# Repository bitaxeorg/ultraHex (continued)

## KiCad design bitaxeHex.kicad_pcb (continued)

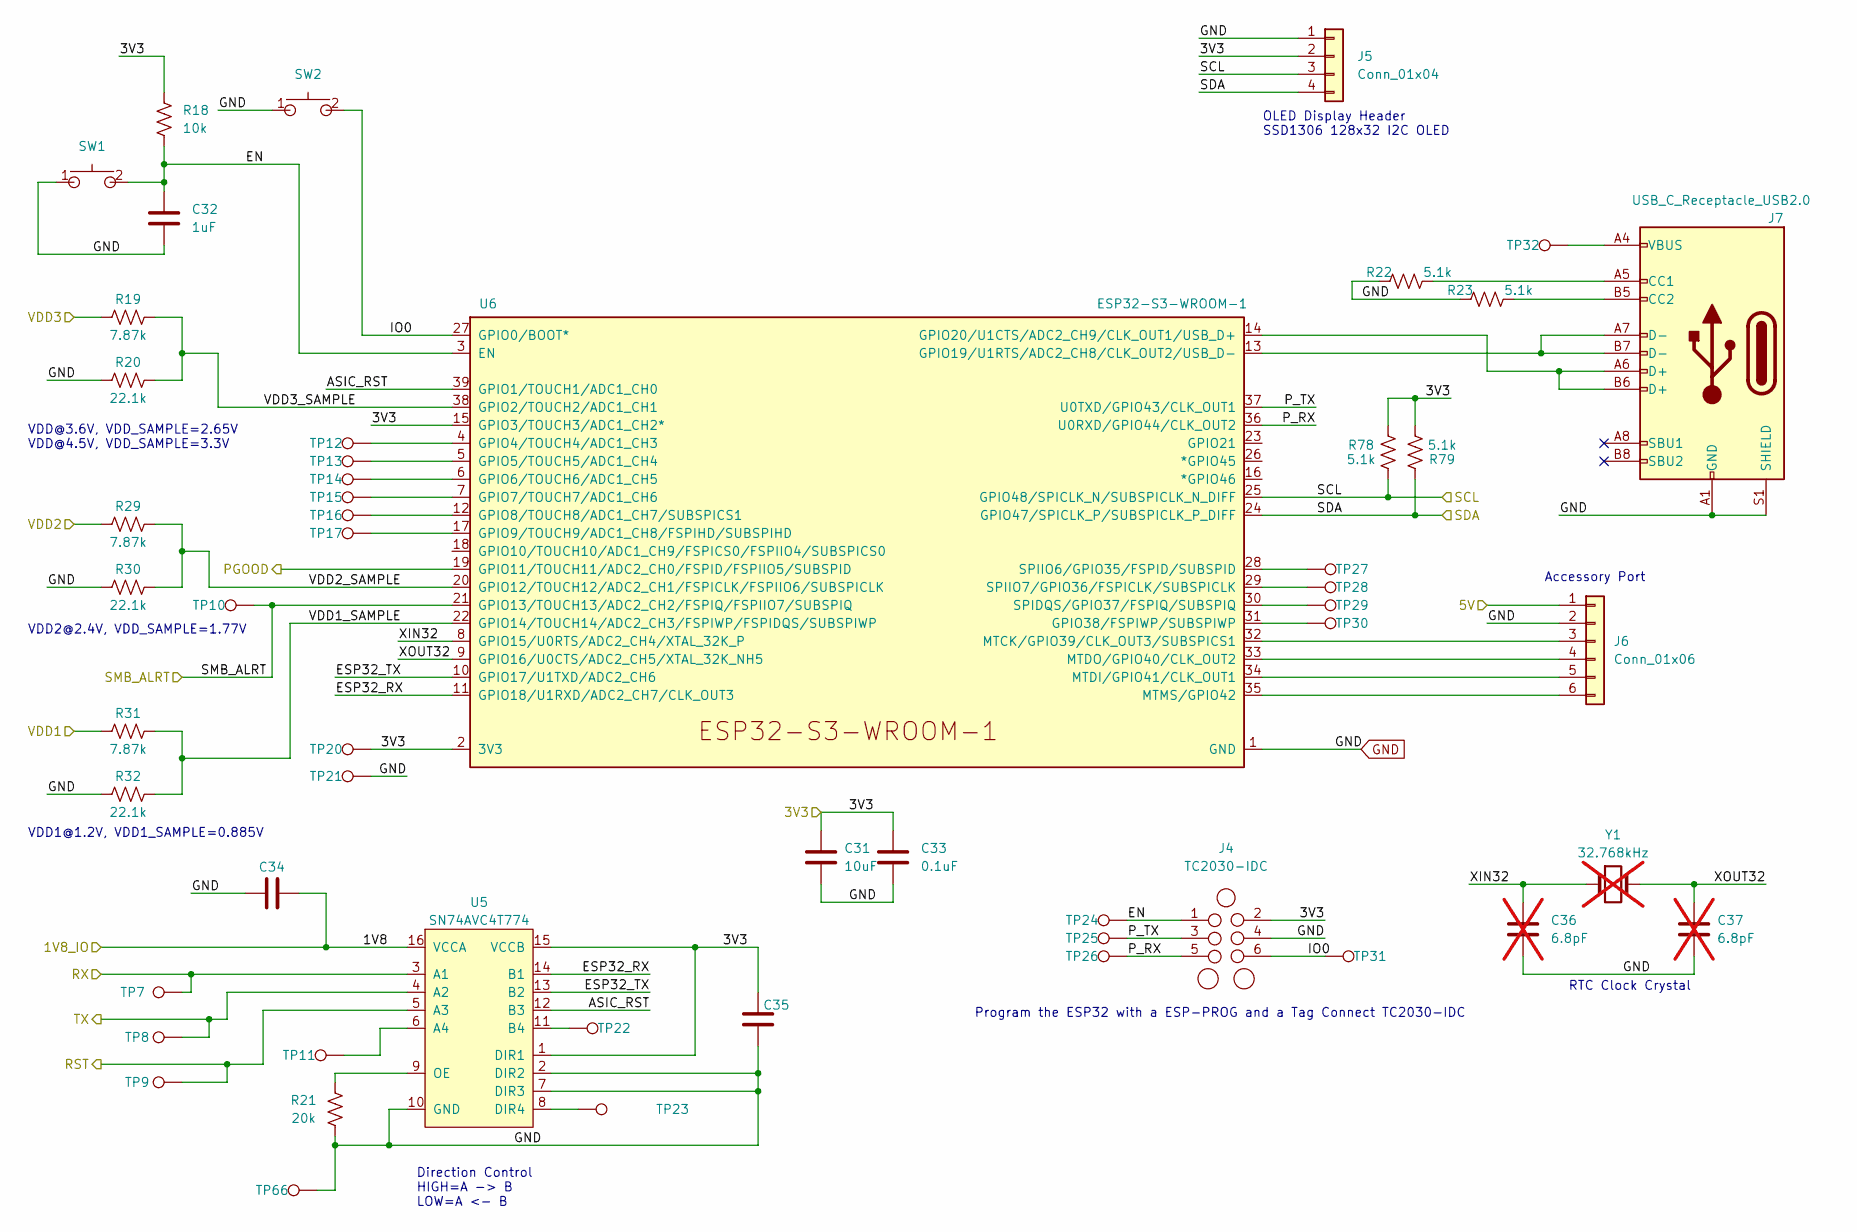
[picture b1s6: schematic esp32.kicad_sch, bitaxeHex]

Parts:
C31: 10uF; C_0805_2012Metric; PARTNO GRM21BR61H106ME43L
C32: 1uF; C_0402_1005Metric; PARTNO EMK105BJ105MV-F
C33: 0.1uF; C_0402_1005Metric; PARTNO KGM05AR71C104KH
C34, C35: 311-3342-1-ND; C_0402_1005Metric; PARTNO KGM05AR71C104KH
C36, C37: 6.8pF; C_0402_1005Metric; PARTNO C0402C689C5GAC7867; not fitted
J4: TC2030-IDC; Tag-Connect_TC2030-IDC-NL_2x03_P1.27mm_Vertical
J5: Conn_01x04; PinHeader_1x04_P2.54mm_Vertical
J6: Conn_01x06; PinHeader_1x06_P2.54mm_Vertical
J7: USB_C_Receptacle_USB2.0; USB_C_Receptacle_GCT_USB4105-xx-A_16P_TopMnt_Horizontal; PARTNO USB4105-GF-A
R18: 10k; R_0402_1005Metric; PARTNO RC0402JR-0710KL
R19, R29, R31: 7.87k; R_0402_1005Metric; PARTNO RC0402FR-077K87L
R20, R30, R32: 22.1k; R_0402_1005Metric; PARTNO RC0402FR-0722K1L
R21: 20k; R_0402_1005Metric; PARTNO RC0402FR-0720KL
R22, R23, R78, R79: 5.1k; R_0402_1005Metric; PARTNO RC0402FR-135K1L
SW1, SW2: SWITCH-SPST; TL3340-switch; PARTNO TL3340AF160QG
TP7, TP8, TP9, TP10, TP11, TP12, TP13, TP14, TP15, TP16, TP17, TP20, TP21, TP22, TP23, TP24, TP25, TP26, TP27, TP28, TP29, TP30, TP31, TP32, TP66: TestPoint; TestPoint_Pad_D1.0mm
U5: SN74AVC4T774; TSSOP-16_4.4x5mm_P0.65mm; PARTNO SN74AVC4T774PWR
U6: ESP32-S3-WROOM-1; ESP32-S3-WROOM-1U; PARTNO ESP32-S3-WROOM-1U-N16R8
Y1: 32.768kHz; SC32S-7PF20PPM; PARTNO SC32S-7PF20PPM; not fitted

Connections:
/1V8: C34.2, U5.16 (VCCA); also elsewhere on the board
/3V3: C31.1, C33.1, C35.1, J4.2, J5.2, R18.1, R78.2, R79.1, TP20.1 (1_1), U5.1 (DIR1), U5.15 (VCCB), U6.2 (3V3), U6.15 (GPIO3/TOUCH3/ADC1_CH2*); also elsewhere on the board
/5V: J6.1; also elsewhere on the board
/CI: TP8.1 (1_1), U5.4 (A2); also elsewhere on the board
/ESP32/ASIC_RST: U5.12 (B3), U6.39 (GPIO1/TOUCH1/ADC1_CH0)
/ESP32/EN: C32.1, J4.1, R18.2, SW1.2, TP24.1 (1_1), U6.3 (EN)
/ESP32/ESP32_RX: U5.14 (B1), U6.11 (GPIO18/U1RXD/ADC2_CH7/CLK_OUT3)
/ESP32/ESP32_TX: U5.13 (B2), U6.10 (GPIO17/U1TXD/ADC2_CH6)
/ESP32/IO0: J4.6, SW2.2, TP31.1 (1_1), U6.27 (GPIO0/BOOT*)
/ESP32/P_RX: J4.5, TP26.1 (1_1), U6.36 (U0RXD/GPIO44/CLK_OUT2)
/ESP32/P_TX: J4.3, TP25.1 (1_1), U6.37 (U0TXD/GPIO43/CLK_OUT1)
/ESP32/VDD1_SAMPLE: R31.1, R32.2, U6.22 (GPIO14/TOUCH14/ADC2_CH3/FSPIWP/FSPIDQS/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)
/ESP32/VDD2_SAMPLE: R29.1, R30.2, U6.20 (GPIO12/TOUCH12/ADC2_CH1/FSPICLK/FSPIIO6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)
/ESP32/VDD3_SAMPLE: R19.1, R20.2, U6.38 (GPIO2/TOUCH2/ADC1_CH1)
/ESP32/XIN32: C36.1, U6.8 (GPIO15/U0RTS/ADC2_CH4/XTAL_32K_P), Y1.1
/ESP32/XOUT32: C37.1, U6.9 (GPIO16/U0CTS/ADC2_CH5/XTAL_32K_NH5), Y1.2
/NRSTI: TP9.1 (1_1), U5.5 (A3); also elsewhere on the board
/Power/PGOOD: U6.19 (GPIO11/TOUCH11/ADC2_CH0/FSPID/FSPIIO5/S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); also elsewhere on the board
/RO: TP7.1 (1_1), U5.3 (A1); also elsewhere on the board
/SCL: J5.3, R78.1, U6.25 (GPIO48/SPICLK_N/SUBSPICLK_N_DIFF); also elsewhere on the board
/SDA: J5.4, R79.2, U6.24 (GPIO47/SPICLK_P/SUBSPICLK_P_DIFF); also elsewhere on the board
/SMB_ALRT: TP10.1 (1_1), U6.21 (GPIO13/TOUCH13/ADC2_CH2/FSPIQ/FSPIIO7/S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); also elsewhere on the board
/VDD: R19.2; also elsewhere on the board
/VDD1: R31.2; also elsewhere on the board
/VDD2: R29.2; also elsewhere on the board
GND: C31.2, C32.2, C33.2, C34.1, C35.2, C36.2, C37.2, J4.4, J5.1, J6.2, J7.A1 (GND), J7.A12 (GND), J7.B1 (GND), J7.B12 (GND), J7.S1 (SHIELD), R20.1, R21.1, R22.1, R23.1, R30.1, R32.1, SW1.1, SW2.1, TP21.1 (1_1), TP66.1 (1_1), U5.2 (DIR2), U5.7 (DIR3), U5.10 (GND), U6.1 (GND), U6.40 (GND), U6.41 (GND); also elsewhere on the board
unnamed: J6.3, U6.32 (MTCK/GPIO39/CLK_OUT3/SUBSPICS1)
unnamed: J6.4, U6.33 (MTDO/GPIO40/CLK_OUT2)
unnamed: J6.5, U6.34 (MTDI/GPIO41/CLK_OUT1)
unnamed: J6.6, U6.35 (MTMS/GPIO42)
unnamed: J7.A5 (CC1), R22.2
unnamed: J7.B5 (CC2), R23.2
unnamed: J7.A4 (VBUS), J7.A9 (VBUS), J7.B4 (VBUS), J7.B9 (VBUS), TP32.1 (1_1)
unnamed: TP11.1 (1_1), U5.6 (A4)
unnamed: TP22.1 (1_1), U5.11 (B4)
unnamed: TP23.1 (1_1), U5.8 (DIR4)
unnamed: R21.2, U5.9 (OE)
unnamed: TP12.1 (1_1), U6.4 (GPIO4/TOUCH4/ADC1_CH3)
unnamed: TP13.1 (1_1), U6.5 (GPIO5/TOUCH5/ADC1_CH4)
unnamed: TP14.1 (1_1), U6.6 (GPIO6/TOUCH6/ADC1_CH5)
unnamed: TP15.1 (1_1), U6.7 (GPIO7/TOUCH7/ADC1_CH6)
unnamed: TP16.1 (1_1), U6.12 (GPIO8/TOUCH8/ADC1_CH7/SUBSPICS1)
unnamed: TP17.1 (1_1), U6.17 (GPIO9/TOUCH9/ADC1_CH8/FSPIHD/SUBSPIHD)
unnamed: J7.A7 (D-), J7.B7 (D-), U6.13 (GPIO19/U1RTS/ADC2_CH8/CLK_OUT2/USB_D-)
unnamed: J7.A6 (D+), J7.B6 (D+), U6.14 (GPIO20/U1CTS/ADC2_CH9/CLK_OUT1/USB_D+)
unnamed: TP30.1 (1_1), U6.31 (GPIO38/FSPIWP/SUBSPIWP)
unnamed: TP29.1 (1_1), U6.30 (SPIDQS/GPIO37/FSPIQ/SUBSPIQ)
unnamed: TP27.1 (1_1), U6.28 (SPIIO6/GPIO35/FSPID/SUBSPID)
unnamed: TP28.1 (1_1), U6.29 (SPIIO7/GPIO36/FSPICLK/SUBSPICLK)

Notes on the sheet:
OLED Display Header SSD1306 128x32 I2C OLED
RTC Clock Crystal
Accessory Port
Program the ESP32 with a ESP-PROG and a Tag Connect TC2030-IDC
VDD2@2.4V, VDD_SAMPLE=1.77V
VDD@3.6V, VDD_SAMPLE=2.65V VDD@4.5V, VDD_SAMPLE=3.3V
Direction Control HIGH=A -> B LOW=A <- B
VDD1@1.2V, VDD1_SAMPLE=0.885V

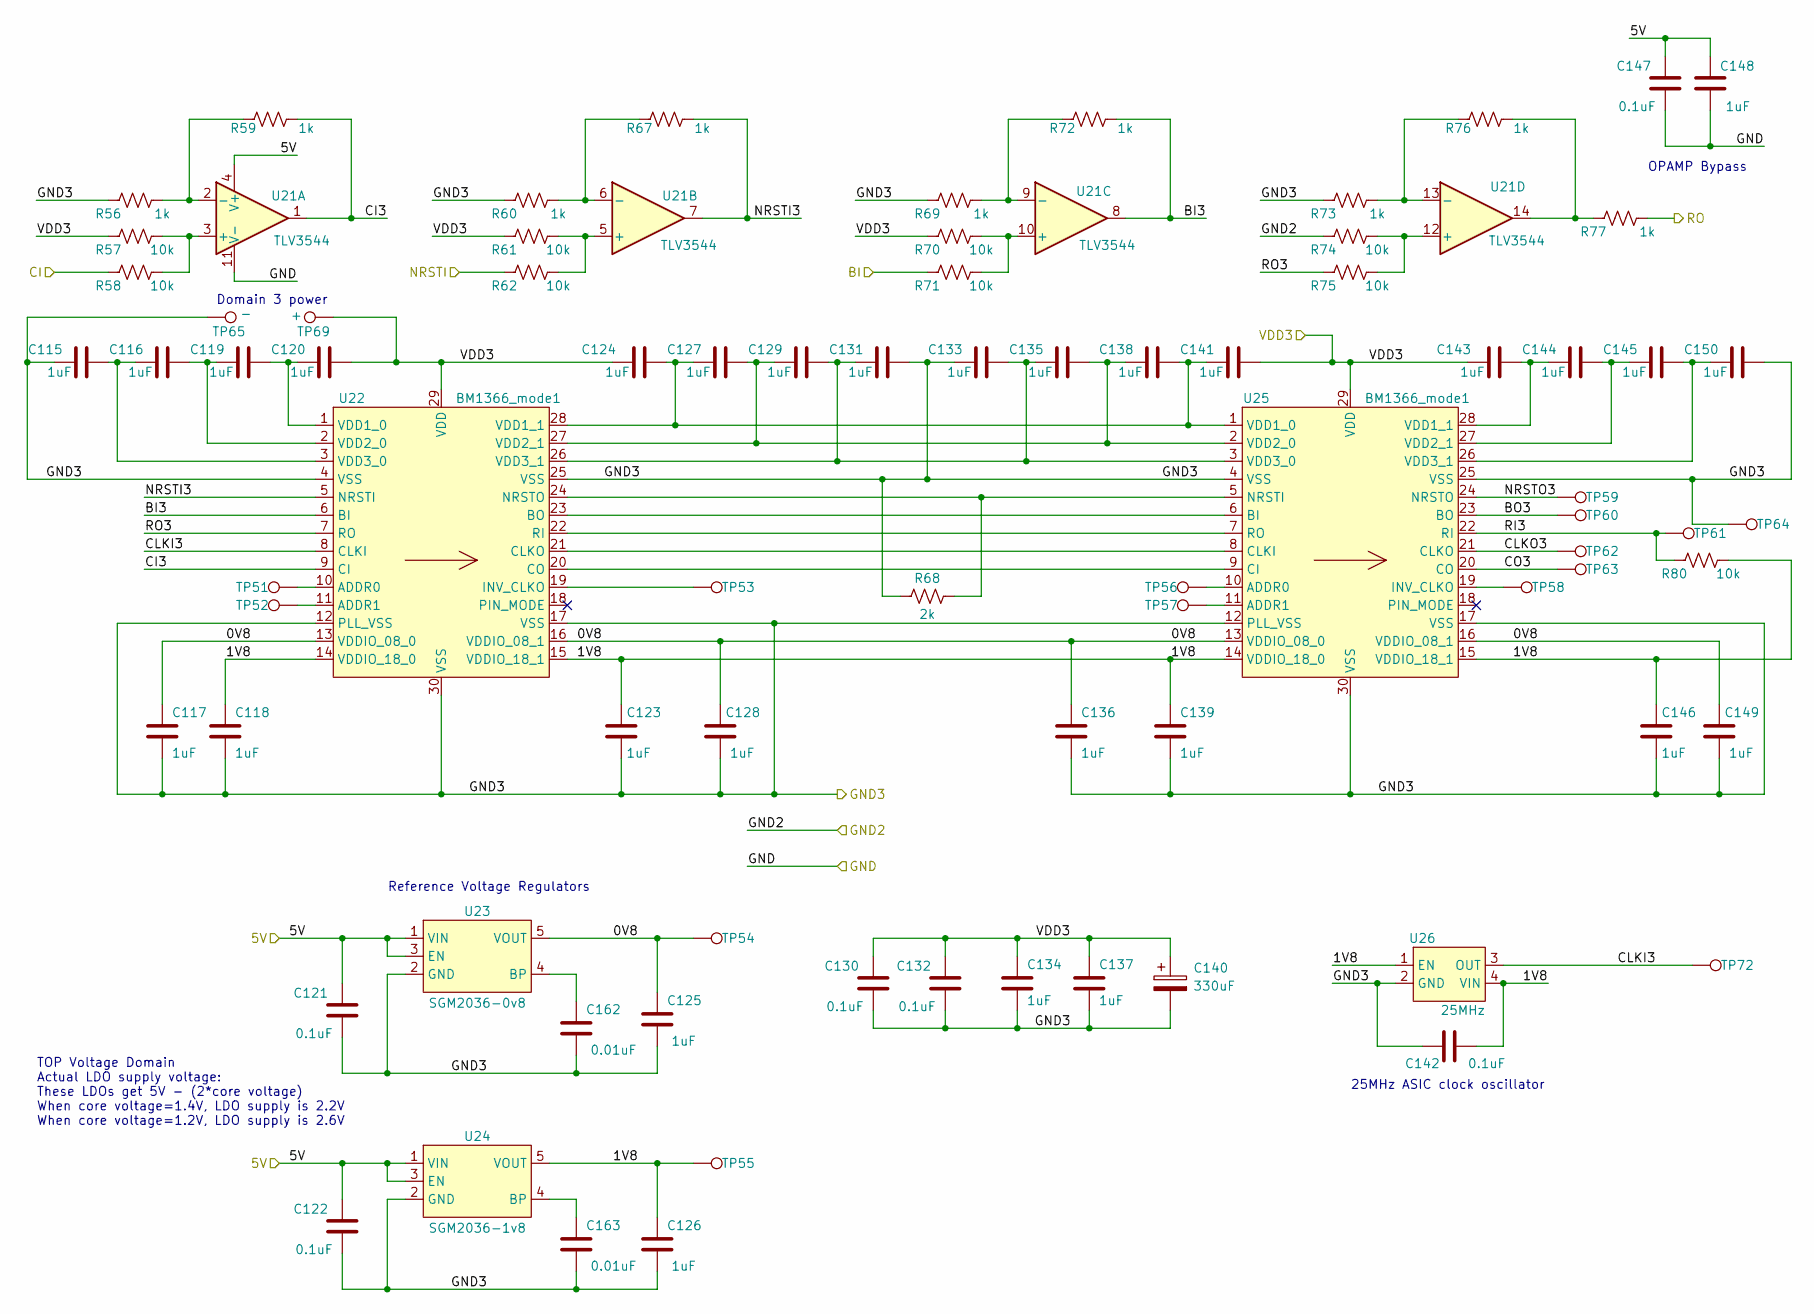
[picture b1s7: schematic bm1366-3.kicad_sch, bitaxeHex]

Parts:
C115, C116, C117, C118, C119, C120, C123, C124, C125, C126, C127, C128, C129, C131, C133, C134, C135, C136, C137, C138, C139, C141, C143, C144, C145, C146, C148, C149, C150: 1uF; C_0402_1005Metric; PARTNO EMK105BJ105MV-F
C121, C122, C130, C132, C142, C147: 0.1uF; C_0402_1005Metric; PARTNO KGM05AR71C104KH
C140: 330uF; CP_EIA-7343-31_Kemet-D_Pad2.25x2.55mm_HandSolder; PARTNO 293D337X9010E2TE3
C162, C163: 0.01uF; C_0402_1005Metric; PARTNO KGM05AR70J103KH
R56, R59, R60, R67, R69, R72, R73, R76, R77: 1k; R_0402_1005Metric; PARTNO RC0402FR-071KL
R57, R58, R61, R62, R70, R71, R74, R75, R80: 10k; R_0402_1005Metric; PARTNO RC0402JR-0710KL
R68: 2k; R_0402_1005Metric; PARTNO RT0402BRD072KL
TP51, TP52, TP53, TP56, TP57, TP58: TestPoint; TestPoint_Pad_D1.0mm
TP54, TP55, TP72: TestPoint; TestPoint_Pad_D1.0mm_highlight
TP59, TP60, TP61, TP62, TP63, TP64: TestPoint; TestPoint_Pad_D1.5mm
TP65: -; TestPoint_Pad_D1.5mm
TP69: +; TestPoint_Pad_D1.5mm
U21: TLV3544; TSSOP-14_4.4x5mm_P0.65mm; PARTNO TLV3544IPWR
U22, U25: BM1366_mode1; BM1366
U23: SGM2036-0v8; TSOT-23-5; PARTNUM SGM2036-0.8YN5G/TR
U24: SGM2036-1v8; TSOT-23-5; PARTNUM SGM2036-1.8YN5G/TR
U26: 25MHz; O 25,0-JO32-B-1V3-1-T1-LF; PARTNO O 25,0-JO32-B-1V3-1-T1-LF

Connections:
/5V: C121.2, C122.2, C147.2, C148.2, U21.4 (V+), U23.1 (VIN), U23.3 (EN), U24.1 (VIN), U24.3 (EN); also elsewhere on the board
/BM1366-2/BO: R71.1; also elsewhere on the board
/BM1366-2/CO: R58.1; also elsewhere on the board
/BM1366-2/NRSTO: R62.1; also elsewhere on the board
/BM1366-2/RI: R77.1; also elsewhere on the board
/BM1366-3/0V8: C117.1, C125.1, C128.1, C136.1, C149.1, TP54.1 (1_1), U22.13 (VDDIO_08_0), U22.16 (VDDIO_08_1), U23.5 (VOUT), U25.13 (VDDIO_08_0), U25.16 (VDDIO_08_1)
/BM1366-3/1V8: C118.1, C123.1, C126.1, C139.1, C142.1, C146.1, R80.2, TP55.1 (1_1), U22.14 (VDDIO_18_0), U22.15 (VDDIO_18_1), U24.5 (VOUT), U25.14 (VDDIO_18_0), U25.15 (VDDIO_18_1), U26.1 (EN), U26.4 (VIN)
/BM1366-3/BI3: R72.1, U21.8, U22.6 (BI)
/BM1366-3/BO3: TP60.1 (1_1), U25.23 (BO)
/BM1366-3/CI3: R59.1, U21.1, U22.9 (CI)
/BM1366-3/CLKI3: TP72.1 (1_1), U22.8 (CLKI), U26.3 (OUT)
/BM1366-3/CLKO3: TP62.1 (1_1), U25.21 (CLKO)
/BM1366-3/CO3: TP63.1 (1_1), U25.20 (CO)
/BM1366-3/NRSTI3: R67.1, U21.7, U22.5 (NRSTI)
/BM1366-3/NRSTO3: TP59.1 (1_1), U25.24 (NRSTO)
/BM1366-3/RI3: R80.1, TP61.1 (1_1), U25.22 (RI)
/BM1366-3/RO3: R75.1, U22.7 (RO)
/VDD: C120.2, C124.1, C130.2, C132.2, C134.1, C137.1, C140.1, C141.2, C143.1, R57.1, R61.1, R70.1, TP69.1 (1_1), U22.29 (VDD), U25.29 (VDD); also elsewhere on the board
/VDD1: R74.1; also elsewhere on the board
/VDD2: C115.1, C117.2, C118.2, C121.1, C122.1, C123.2, C125.2, C126.2, C128.2, C130.1, C131.2, C132.1, C133.1, C134.2, C136.2, C137.2, C139.2, C140.2, C142.2, C146.2, C149.2, C150.2, C162.2, C163.2, R56.2, R60.2, R68.1, R69.2, R73.2, TP64.1 (1_1), TP65.1 (1_1), U22.4 (VSS), U22.12 (PLL_VSS), U22.17 (VSS), U22.25 (VSS), U22.30 (VSS), U23.2 (GND), U24.2 (GND), U25.4 (VSS), U25.12 (PLL_VSS), U25.17 (VSS), U25.25 (VSS), U25.30 (VSS), U26.2 (GND); also elsewhere on the board
GND: C147.1, C148.1, U21.11 (V-); also elsewhere on the board
unnamed: R76.1, R77.2, U21.14
unnamed: R57.2, R58.2, U21.3 (+)
unnamed: R56.1, R59.2, U21.2 (-)
unnamed: R61.2, R62.2, U21.5 (+)
unnamed: R60.1, R67.2, U21.6 (-)
unnamed: R70.2, R71.2, U21.10 (+)
unnamed: R69.1, R72.2, U21.9 (-)
unnamed: R74.2, R75.2, U21.12 (+)
unnamed: R73.1, R76.2, U21.13 (-)
unnamed: TP51.1 (1_1), U22.10 (ADDR0)
unnamed: TP52.1 (1_1), U22.11 (ADDR1)
unnamed: U22.23 (BO), U25.6 (BI)
unnamed: U22.21 (CLKO), U25.8 (CLKI)
unnamed: U22.20 (CO), U25.9 (CI)
unnamed: TP53.1 (1_1), U22.19 (INV_CLKO)
unnamed: R68.2, U22.24 (NRSTO), U25.5 (NRSTI)
unnamed: U22.22 (RI), U25.7 (RO)
unnamed: C119.2, C120.1, U22.1 (VDD1_0)
unnamed: C124.2, C127.1, C138.2, C141.1, U22.28 (VDD1_1), U25.1 (VDD1_0)
unnamed: C116.2, C119.1, U22.2 (VDD2_0)
unnamed: C127.2, C129.1, C135.2, C138.1, U22.27 (VDD2_1), U25.2 (VDD2_0)
unnamed: C115.2, C116.1, U22.3 (VDD3_0)
unnamed: C129.2, C131.1, C133.2, C135.1, U22.26 (VDD3_1), U25.3 (VDD3_0)
unnamed: C162.1, U23.4 (BP)
unnamed: C163.1, U24.4 (BP)
unnamed: TP56.1 (1_1), U25.10 (ADDR0)
unnamed: TP57.1 (1_1), U25.11 (ADDR1)
unnamed: TP58.1 (1_1), U25.19 (INV_CLKO)
unnamed: C143.2, C144.1, U25.28 (VDD1_1)
unnamed: C144.2, C145.1, U25.27 (VDD2_1)
unnamed: C145.2, C150.1, U25.26 (VDD3_1)

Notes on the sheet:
25MHz ASIC clock oscillator
Domain 3 power
Reference Voltage Regulators
OPAMP Bypass
TOP Voltage Domain Actual LDO supply voltage: These LDOs get 5V - (2*core voltage) When core voltage=1.4V, LDO supply is 2.2V When core voltage=1.2V, LDO supply is 2.6V

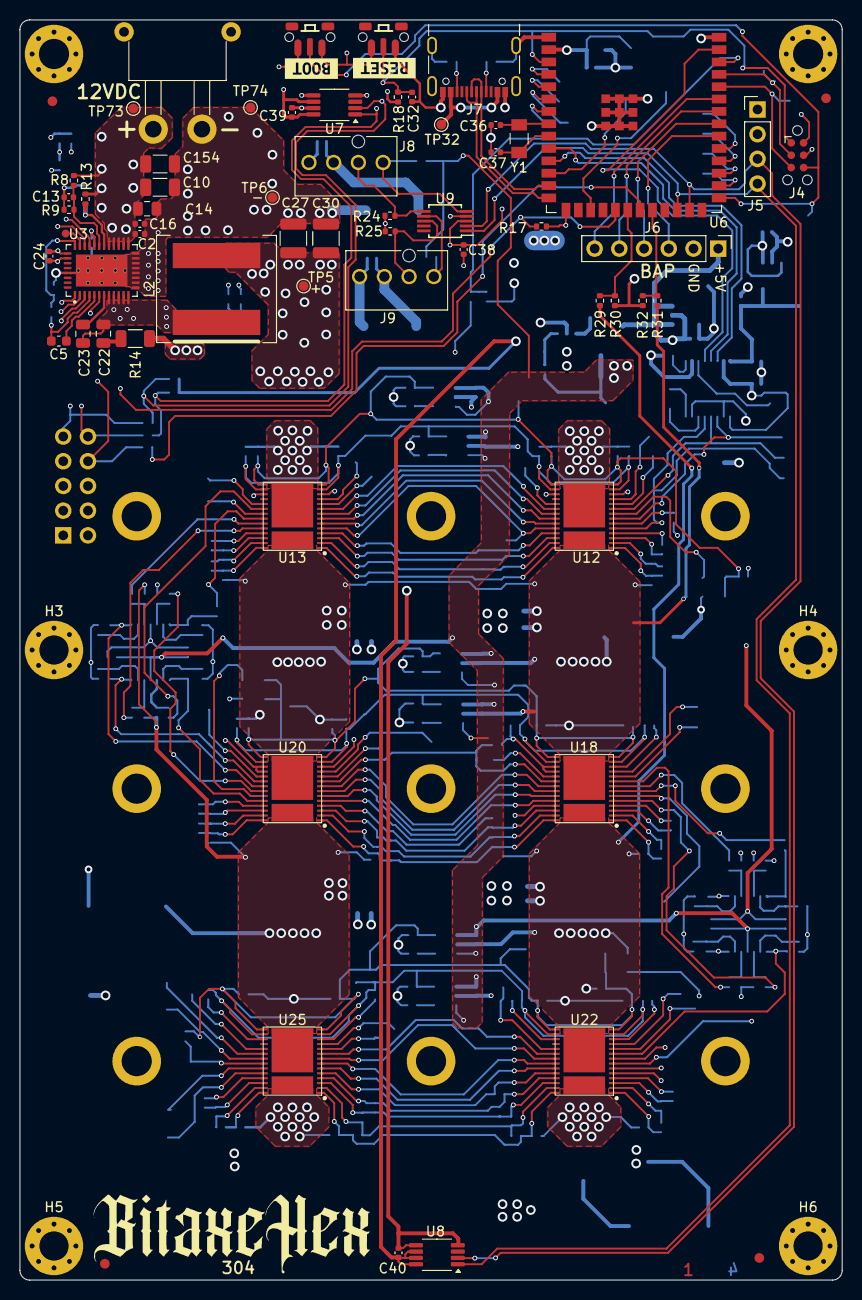
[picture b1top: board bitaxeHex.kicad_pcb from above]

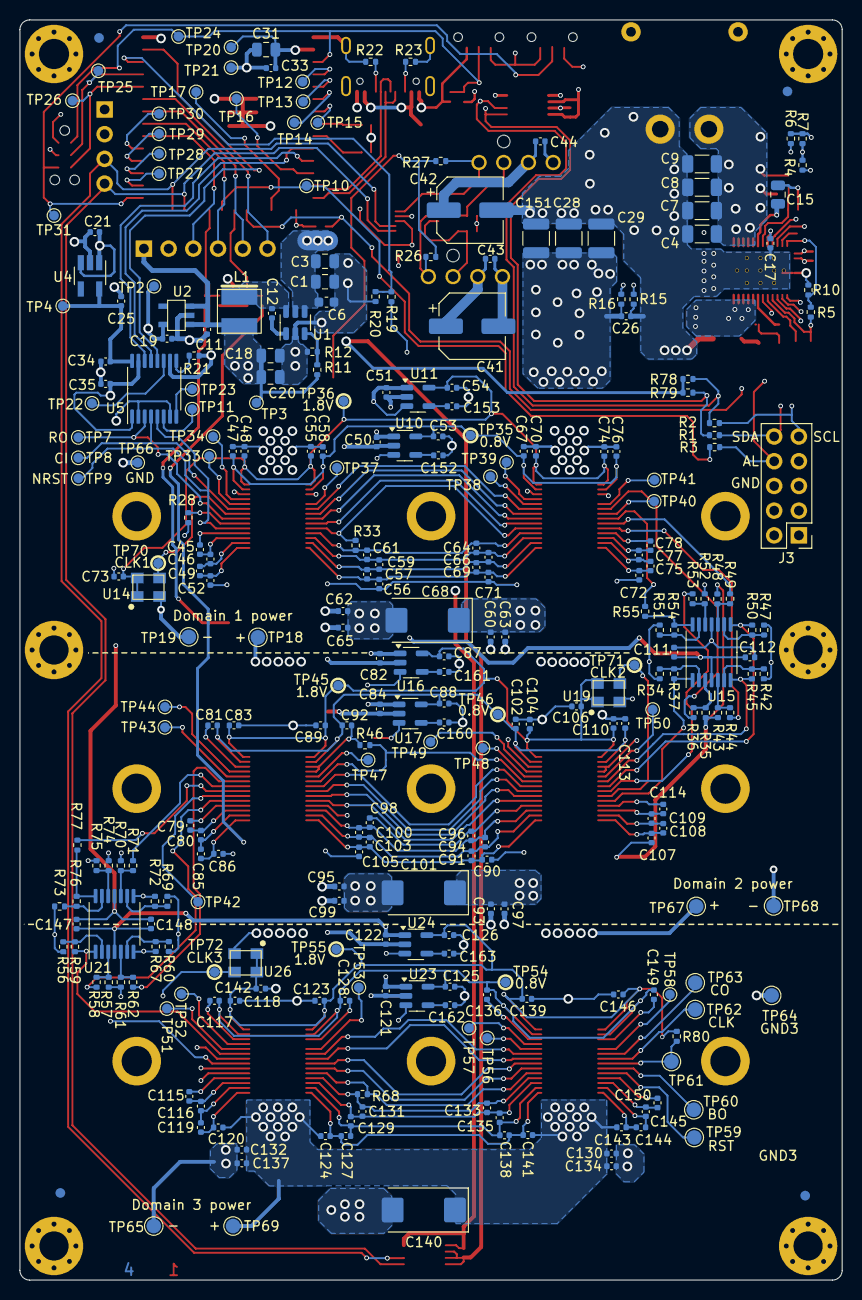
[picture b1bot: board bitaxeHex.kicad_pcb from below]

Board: 4 copper layers, 84.5 x 129.5 mm, 369 parts (289 on the bottom side), 192 nets.

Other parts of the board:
kibuzzard-65356D4E: G***; kibuzzard-65356D4E
kibuzzard-65356D5C: G***; kibuzzard-65356D5C

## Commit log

2025-02-20 add instructions for v304 modification to README
2025-02-20 add v304 fix to schematic
2025-03-17 Update LICENSE
2025-04-03 supply latest gerbers for v304
